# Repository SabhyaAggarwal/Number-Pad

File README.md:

# Number Pad
This is a keyboard made by me that acts as a number pad for many keyboards today that don't include it, and it's designed for use in, say, the calculator app. The PCB was designed in Ki-CAD, the case was designed in Onshape, and it uses QMK firmware. As per me, the  design and shape is beautiful...

## BOM
|Name                    |Description                                                                        |Quantity|Total Cost|Link                                                                                                          |Distributor       |
|------------------------|-----------------------------------------------------------------------------------|--------|----------|--------------------------------------------------------------------------------------------------------------|------------------|
|PCB                     |Main PCB(includes payment fee)                                                     |1       |$1.36     |https://aivon.com/                                                                                            |AIVON             |
|Seeed Studio XIAO RP2040|Main Dev Board(cost includes shipping)                                             |1       |$8.72     |https://sharvielectronics.com/product/xiao-rp2040-supports-arduino-micropython-and-circuitpython-seeed-studio/|sharvi electronics|
|MX Switches             |MX switches(pack of 10 and 2 of them = 20 keys)(includes shipping)                 |2       |$5.11     |https://stackskb.com/store/click-inc-hp-switch-pack-of-10-pre-order/                                          |stackskb          |
|Keycaps                 |Numpad keycaps(shipping grouped with switches)                                     |1       |$1.57     |https://stackskb.com/store/numpad-keycaps/?attribute_variant=MDA+Lavender                                     |stackskb          |
|1N4148 Diode            |1N4148 Diode(price not include shipping as shipping is shared with the XIAO RP2040)|17      |$0.60     |https://sharvielectronics.com/product/1n4148-small-signal-fast-switching-diodes-do-35-package/                |sharvi electronics              |
|2u MX Stabilizers       |Stabilizers(shipping grouped with switches)                                        |3       |$3.13     |https://stackskb.com/store/genuine-cherry-mx-plate-mount-stabilizers-2u/                                      |stackskb          |

## Images

### CAD
#### 3D Renders of the Number Pad

#### 3D render of Case

#### 3D render of Plate

###### Note: Earlier I decided I would have an OLED. Later I decided I should not. [This](https://cad.onshape.com/documents/dad228ea60076f74a46a1f61/w/2f4558e967e48aff5bcd16fe/e/fbd68186b11d7caaa4edcef6?renderMode=0&uiState=6ab79fd89886a45a7fd9a169) link is for the one which shows the OLED would be there but actually we're not going to place it that way. I am just giving that link because it has the exact correct placements and it also has the plate and case Part Studio, and for the one with none. of them, it's [this](https://cad.onshape.com/documents/9043f20461557082fc912c61/w/6b8636902849ed63c82f6d7b/e/4d242b45682191a3636d33f8?renderMode=0&uiState=6ab79ffff660f4859433cc5e)...
### PCB

#### 3D render of PCB

#### PCB layout 

#### Schematic

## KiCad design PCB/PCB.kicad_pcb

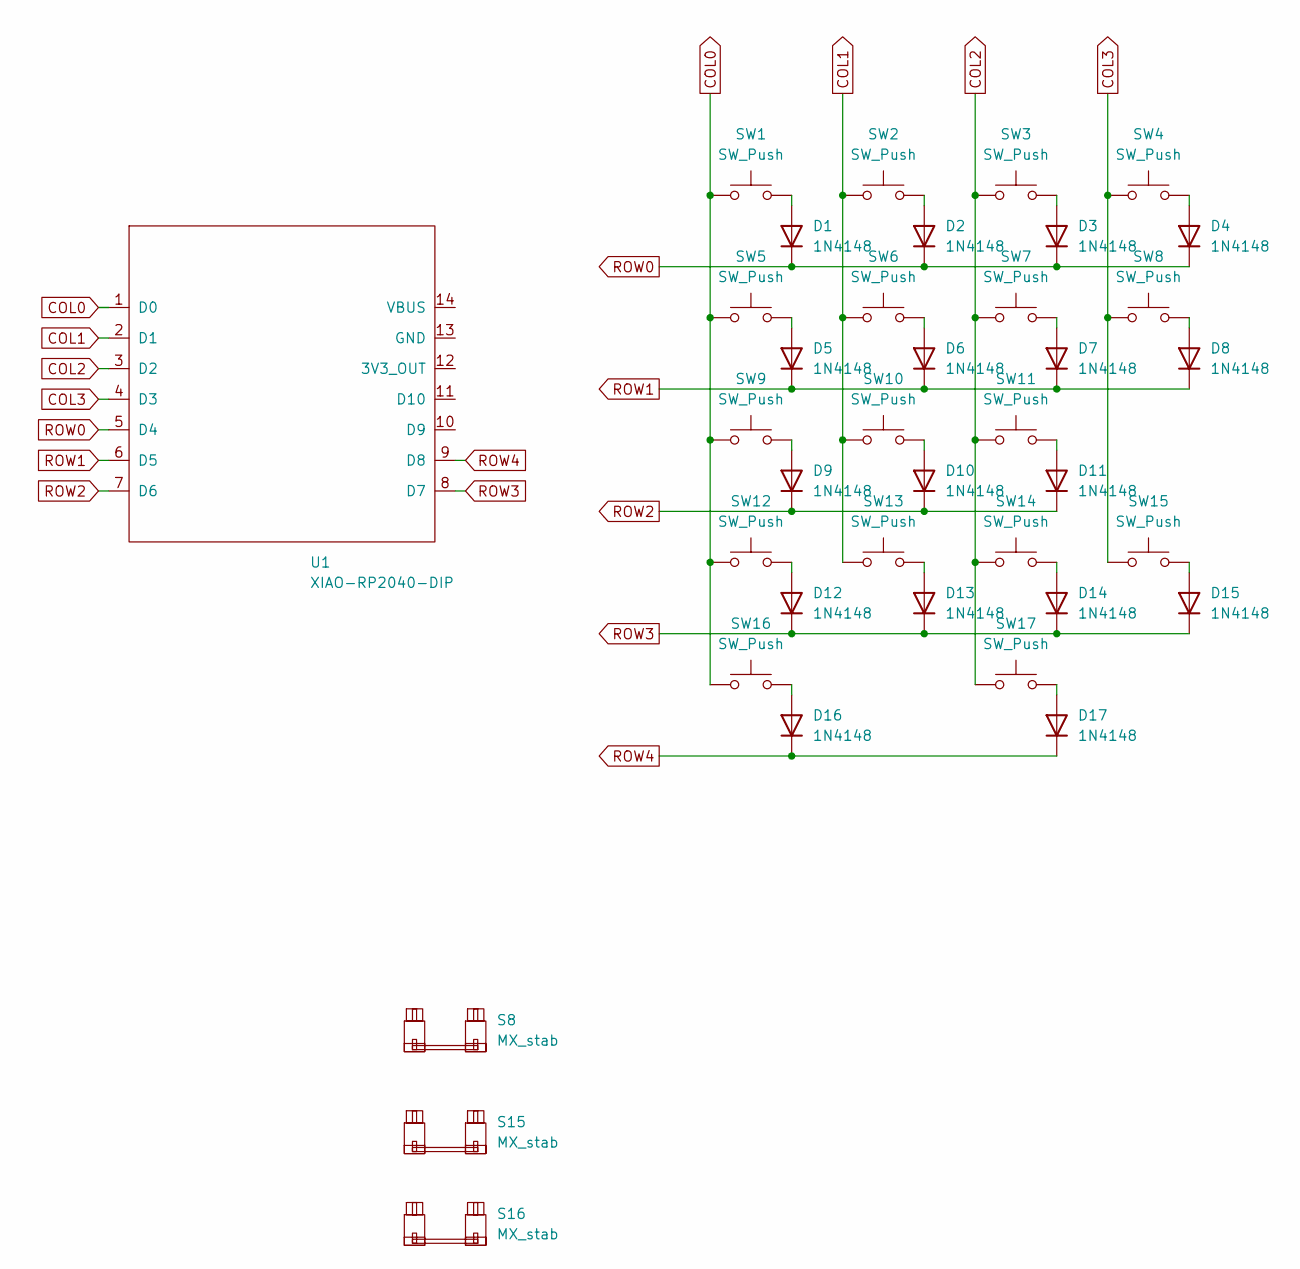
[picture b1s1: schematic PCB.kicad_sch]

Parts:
D1, D2, D3, D4, D5, D6, D7, D8, D9, D10, D11, D12, D13, D14, D15, D16, D17: 1N4148; D_DO-35_SOD27_P7.62mm_Horizontal
S8, S15, S16: MX_stab; STAB_MX_2u
SW1, SW2, SW3, SW4, SW5, SW6, SW7, SW8, SW9, SW10, SW11, SW12, SW13, SW14, SW15, SW16, SW17: SW_Push; SW_MX_1u
U1: XIAO-RP2040-DIP

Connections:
COL0: SW1.1, SW5.1, SW9.1, SW12.1, SW16.1, U1.1 (D0)
COL1: SW2.1, SW6.1, SW10.1, SW13.1, U1.2 (D1)
COL2: SW3.1, SW7.1, SW11.1, SW14.1, SW17.1, U1.3 (D2)
COL3: SW4.1, SW8.1, SW15.1, U1.4 (D3)
unnamed: D1.2 (A), SW1.2
unnamed: D2.2 (A), SW2.2
unnamed: D3.2 (A), SW3.2
unnamed: D4.2 (A), SW4.2
unnamed: D5.2 (A), SW5.2
unnamed: D6.2 (A), SW6.2
unnamed: D7.2 (A), SW7.2
unnamed: D8.2 (A), SW8.2
unnamed: D9.2 (A), SW9.2
unnamed: D10.2 (A), SW10.2
unnamed: D11.2 (A), SW11.2
unnamed: D12.2 (A), SW12.2
unnamed: D13.2 (A), SW13.2
unnamed: D14.2 (A), SW14.2
unnamed: D15.2 (A), SW15.2
unnamed: D16.2 (A), SW16.2
unnamed: D17.2 (A), SW17.2
ROW0: D1.1 (K), D2.1 (K), D3.1 (K), D4.1 (K), U1.5 (D4)
ROW1: D5.1 (K), D6.1 (K), D7.1 (K), D8.1 (K), U1.6 (D5)
ROW2: D9.1 (K), D10.1 (K), D11.1 (K), U1.7 (D6)
ROW3: D12.1 (K), D13.1 (K), D14.1 (K), D15.1 (K), U1.8 (D7)
ROW4: D16.1 (K), D17.1 (K), U1.9 (D8)

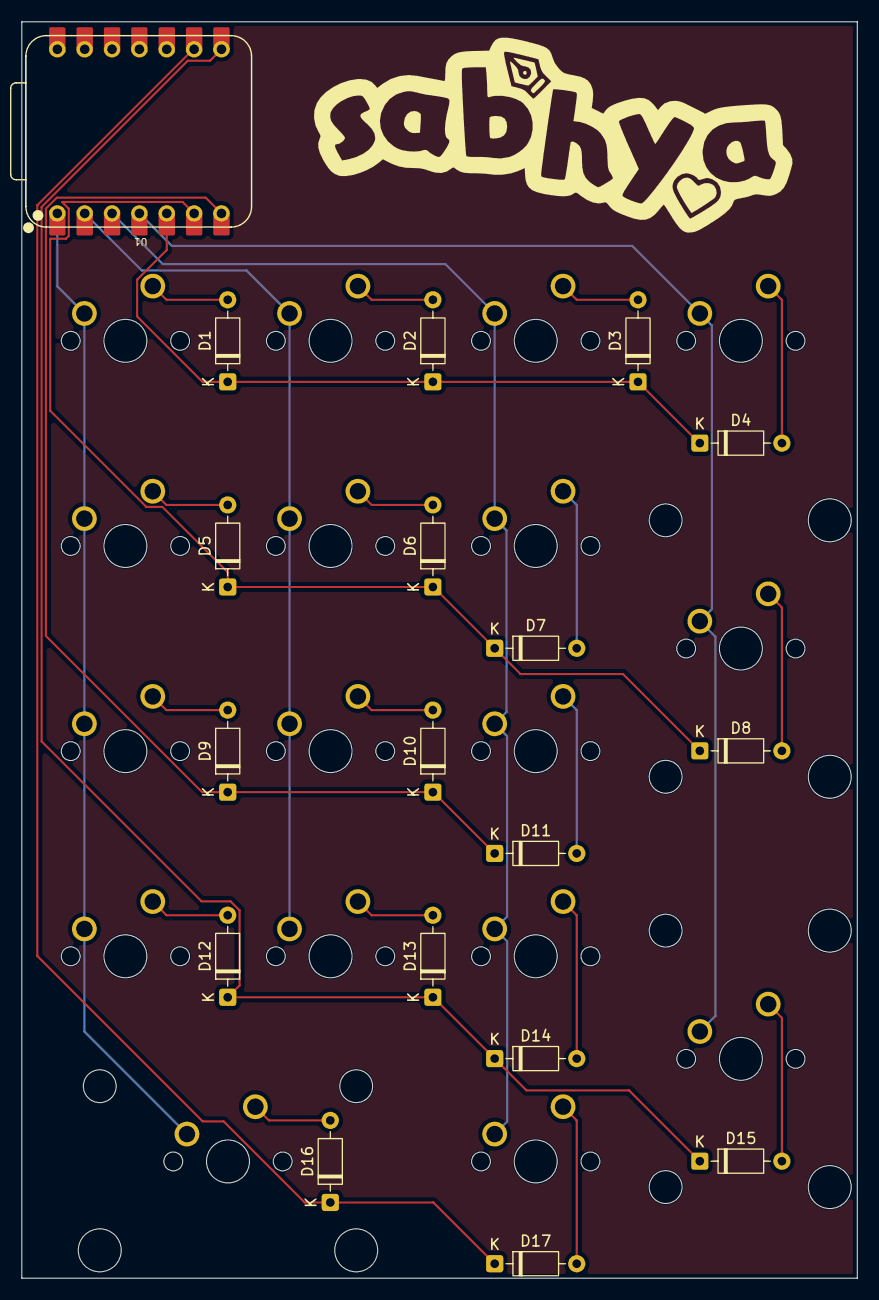
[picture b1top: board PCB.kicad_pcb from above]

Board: 2 copper layers, 77.6 x 116.7 mm, 38 parts (0 on the bottom side), 26 nets.
